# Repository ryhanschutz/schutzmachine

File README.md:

<div align="center">

### Painel Digital de Telemetria Automotiva Stand-Alone — Protocolo CAN / OBD-II
**Hardware aberto embarcado em ESP32-S3 · Display IPS 4.3" (`480 × 272`) · Shift Light físico 10× LEDs 5mm · Carcaça 3D paramétrica em 3 etapas**

<br/>

<table>
  <tr>
    <td align="center" width="52%">
      <br/>
      <sub><b>Simulação em Perspectiva 3/4</b> — Case 3D montado com friso vermelho, tela ativa e 10 LEDs sincronizados</sub>
    </td>
    <td align="center" width="48%">
      <br/>
      <sub><b>Vista Frontal em Operação</b> — Puxada simulada com curva de RPM, peak-hold e flash de shift-light</sub>
    </td>
  </tr>
</table>

*Teste a interface interativa ao vivo no navegador em [`frontend_preview/index.html`](./frontend_preview/index.html)*

</div>

---

## Desenho Técnico Mecânico (ABNT A2 · Escala 1:1 · 1º Diedro)

<div align="center">
  
  <br/>
  <sub>
    <b>Dimensões externas:</b> <code>154.0 × 105.0 × 35.0 mm</code> (+ <code>6.0 mm</code> pés M4) · <b>Autor:</b> Ryhan Schutz ·
    <a href="./docs/desenho_tecnico/case_ft600_polo_desenho_tecnico.dxf"><b>Baixar .DXF (ZWCAD / AutoCAD)</b></a> ·
    <a href="./docs/desenho_tecnico/case_ft600_polo_desenho_tecnico.pdf"><b>Baixar .PDF Vetorial (A2)</b></a>
  </sub>
</div>

---

## Galeria 3D & Engenharia Mecânica

Modelagem paramétrica (`1 unid. = 1 mm`) com **auditoria física interna** para todos os módulos/conectores, **logo gravada em baixo-relevo** (`0.6 mm` frontal / `0.8 mm` traseira) e impressão em **3 peças sem pintura**.

<table>
  <tr>
    <td align="center" width="50%">
      <br/>
      <sub><b>Montagem Final:</b> Contorno ergonômico com aba anti-sol, 10 LEDs 5mm e logo em baixo-relevo</sub>
    </td>
    <td align="center" width="50%">
      <br/>
      <sub><b>Auditoria Interna:</b> PCB 4.3", plugues JST, 10 LEDs 5mm, SN65HVD230, MP1584EN e Buzzer 12mm</sub>
    </td>
  </tr>
  <tr>
    <td align="center" width="50%">
      <br/>
      <sub><b>Vista Explodida:</b> 3 peças da carenagem + subconjunto eletrônico interno</sub>
    </td>
    <td align="center" width="50%">
      <br/>
      <sub><b>Bandeja 3D:</b> 3 arquivos <code>.STL</code> orientados na mesa (<code>Z_min = 0</code>) com malha fechada</sub>
    </td>
  </tr>
  <tr>
    <td align="center" width="50%">
      <br/>
      <sub><b>Etapa 1 (<code>01_tampa_frontal.stl</code>):</b> 10 sedes escalonadas (Ø 6.4 → Ø 5.25 mm) + 8 torres M3</sub>
    </td>
    <td align="center" width="50%">
      <br/>
      <sub><b>Etapa 3 (<code>03_tampa_traseira.stl</code>):</b> Berços snap-fit dedicados + baia rebaixada para GX16-4P (Ø 16.2 mm)</sub>
    </td>
  </tr>
</table>

| Etapa | Arquivo `.STL` | Material / Cor | Prof. | Parâmetros FDM Recomendados |
| :---: | :--- | :---: | :---: | :--- |
| **01** | [`01_tampa_frontal.stl`](./impressao_3d/01_tampa_frontal.stl) | PETG / ABS **Preto** | `12.0 mm` | Bico `0.4` · Camada `0.20` · 4 perímetros · 25% Gyroid |
| **02** | [`02_anel_vermelho.stl`](./impressao_3d/02_anel_vermelho.stl) | PETG / ABS **Vermelho** | `3.0 mm` | Bico `0.4` · Camada `0.16–0.20` · Sem suportes |
| **03** | [`03_tampa_traseira.stl`](./impressao_3d/03_tampa_traseira.stl) | PETG / ABS **Preto** | `20.0 mm` | Bico `0.4` · Camada `0.20` · 4 perímetros · Suporte sob pés M4 |

---

## Arquitetura & Protocolo CAN

Projetado para **qualquer veículo equipado com barramento CAN / OBD-II (ISO 15765-4)**, conectado via **cabo único destacável (`GX16-4P`)** sem corte no chicote original.

```mermaid
flowchart LR
    subgraph CAR["Veículo com Barramento CAN / OBD-II"]
        OBD["Porta OBD-II J1962<br/>Pino 6: CAN-H | Pino 14: CAN-L<br/>Pino 4/5: GND"]
        FUSE["Pós-Chave 12V (Linha 15)<br/>Add-a-Circuit + Fusível 2A"]
    end

    subgraph HARNESS["Cabo Único Destacável"]
        GX16["Conector Traseiro GX16-4P<br/>1: +12V | 2: GND | 3: CAN-H | 4: CAN-L"]
    end

    subgraph CASE["SchutzMachine (154 × 105 × 35 mm)"]
        TVS["TVS (SMBJ18A) +<br/>Step-Down MP1584EN (12V → 5V)"]
        CAN["Transceiver CAN<br/>SN65HVD230 (3.3V)"]
        ESP["Guition JC4827W543C<br/>ESP32-S3 (Core 0: TWAI / Core 1: LVGL)<br/>IPS 4.3&quot; 480×272 + Touch GT911"]
        LEDS["Shift Light Superior<br/>10× LEDs 5mm (4V · 3Vm · 3Az)"]
        BUZ["Buzzer Piezo 12mm"]
    end

    OBD -->|"Par trançado + GND"| GX16
    FUSE -->|"+12V Pós-Chave"| GX16
    GX16 --> TVS -->|"5V Regulado"| ESP
    GX16 --> CAN <-->|"IO17 (TX) / IO18 (RX)"| ESP
    ESP --> LEDS
    ESP --> BUZ
```

### Cálculo de Marcha & Calibração por Veículo

Como cada veículo possui relações de câmbio, diferencial, tamanho de pneu e faixa de giro próprias, a inferência de marcha depende diretamente da calibração do conjunto mecânico:

$$R_n = \frac{\text{RPM}}{\text{Velocidade (km/h)}}$$

- **Calibração Embarcada (NVS):** Gravação das razões $R_n$ por marcha, faixas de *shift-light* (`SPORT` / `ECO`) e limiares de alerta direto na memória não-volátil do ESP32-S3.
- **Software de Calibração (Roadmap):** Desenvolvimento futuro de um aplicativo dedicado (via USB-C / Wi-Fi) para criar perfis por veículo, editar relações de marcha, curvas de LEDs, PIDs customizados e limites térmicos/elétricos.

---

## Hardware, BOM & Pinagem

<table>
  <tr>
    <td align="center" width="50%">
      <br/>
      <sub><b>SN65HVD230 (3.3 V)</b> — <code>16.5 × 14.5 × 6.0 mm</code></sub>
    </td>
    <td align="center" width="50%">
      <br/>
      <sub><b>MP1584EN (12V → 5V)</b> — <code>22.0 × 17.0 × 4.5 mm</code></sub>
    </td>
  </tr>
</table>

| Componente | Especificação | Dimensões (mm) | Função |
| :--- | :--- | :---: | :--- |
| **Display + MCU** | Guition **JC4827W543C** (ESP32-S3 N4R8 · IPS 4.3" · GT911) | `120.0 × 70.2 × 4.7` | Core 0: CAN/TWAI · Core 1: LVGL 9 |
| **Transceiver CAN** | **SN65HVD230** (3,3 V — `IO17` TX / `IO18` RX) | `16.5 × 14.5 × 6.0` | Interface ISO 15765-4 (500 kbps) |
| **Regulador DC-DC** | **D-SUN MP1584EN** + Diodo TVS **SMBJ18A** | `22.0 × 17.0 × 4.5` | Alimentação 12V → 5.00V protegida |
| **Shift Light** | **10× LEDs difusos 5mm** (4 Verde · 3 Vermelho · 3 Azul) | `Ø 5.0 × 8.6` | Barra superior progressiva + flash |
| **Conector / Buzzer** | **GX16-4P** (painel) + Buzzer Piezo `12 mm` | `Ø 16.2` / `Ø 12.0` | Chicote destacável + alerta sonoro |
| **Fixação** | 8× Insertos **M3** (`Ø 4.2`) + 4× Insertos **M4** (`Ø 5.2`) | — | PCB, fechamento e pés traseiros |

<details>
<summary><b>Pinagem Elétrica (GX16-4P & SN65HVD230) e Telemetria OBD-II Mode 0x01</b></summary>
<br/>

| Pino `GX16-4P` | Origem | Destino Interno | Observação |
| :---: | :--- | :--- | :--- |
| **1** | Pós-Chave 12 V (Fusível 2 A) | `MP1584EN IN+` (+ TVS) | Evitar Linha 30 (não drenar bateria) |
| **2** | OBD-II Pino 4/5 (`GND`) | `GND` comum | Referência única |
| **3** | OBD-II Pino 6 (`CAN-H`) | `SN65HVD230 CANH` | Par trançado com Pino 4 |
| **4** | OBD-II Pino 14 (`CAN-L`) | `SN65HVD230 CANL` | Par trançado com Pino 3 |

| Variável | PID OBD-II | Taxa | Variável | PID OBD-II | Taxa |
| :--- | :---: | :---: | :--- | :---: | :---: |
| **RPM** | `0x0C` | 20–40 Hz | **Temp. Água** | `0x05` | 1 Hz |
| **Velocidade** | `0x0D` | 20–40 Hz | **Temp. Ar (IAT)** | `0x0F` | 1 Hz |
| **TPS (Borboleta)** | `0x11` / `0x49` | 10–20 Hz | **Bateria** | `0x42` | 1 Hz |
| **Carga / Avanço IGN** | `0x04` / `0x0E` | 5–10 Hz | **Nível Tanque** | `0x2F` | 0,2 Hz |
| **MAP (Pressão/Vácuo)** | `0x0B` | 5 Hz | **Marcha** | Calculada | Real-time |

> [!WARNING]
> Ative **`PSRAM ECC`** no firmware do ESP32-S3 N4R8 (eleva a operação de `+65 °C` para `+85 °C` no painel ao sol) e **ajuste o MP1584EN para `5.00 V` em bancada** antes de conectar o display.

</details>

---

## Estrutura & Roadmap

```text
schutzmachine/
├── frontend_preview/           # Simulador interativo 480×272 + 10 LEDs 5mm
├── impressao_3d/               # 3 arquivos .STL prontos p/ fatiamento + bandeja Blender
├── docs/
│   ├── desenho_tecnico/        # Prancha ABNT A2 (.DXF p/ ZWCAD, .PDF vetorial e .PNG)
│   └── images/                 # GIFs 3D animados, renders, auditoria interna e fotos HW
├── gerar_case_ft600_polo.py    # Script paramétrico 3D (Blender / bpy)
└── case_ft600_polo.blend       # Montagem 3D completa com eletrônica interna
```

- [x] **Engenharia Mecânica & Case 3D** — Modelagem paramétrica, auditoria interna, gravação da logo e 3 `.STL` fechados
- [x] **Desenho Técnico ABNT A2** — Prancha 1:1 em 1º diedro (`.DXF` nativo para ZWCAD + `.PDF`)
- [x] **Simulador UI & Demos 3D** — Tela `480 × 272` interativa + GIFs da carcaça montada em operação
- [ ] **Firmware ESP32-S3 (LVGL 9 + TWAI CAN)** — Polling OBD-II ativo, renderização 60 FPS e controle dos 10 LEDs
- [ ] **Software de Calibração** — Ferramenta externa para perfis de veículos, relações de marcha, shift-light e alertas
- [ ] **Validação em Bancada & Impressão Final** — Montagem PETG/ABS, insertos M3/M4 e testes em veículo CAN

---

<div align="center">
  <sub>Projeto desenvolvido por <b>Ryhan Schutz</b> · Hardware Aberto & Engenharia Mecânica</sub>
</div>

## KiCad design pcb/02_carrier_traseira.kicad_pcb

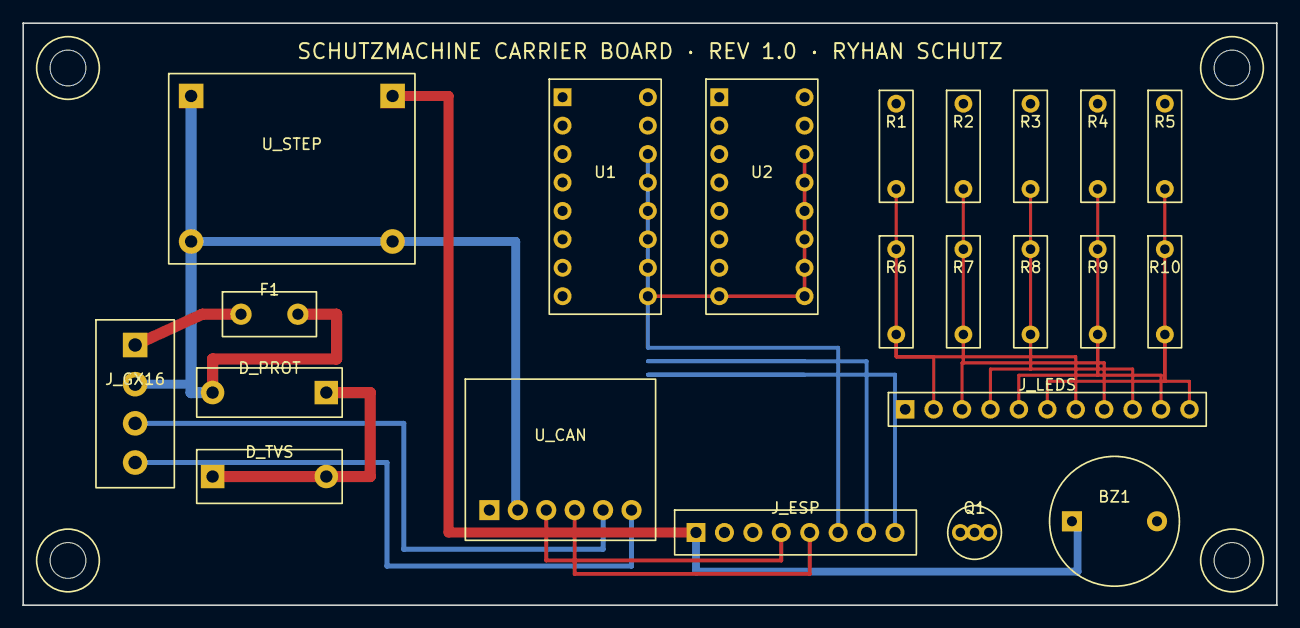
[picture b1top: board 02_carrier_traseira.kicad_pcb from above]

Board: 2 copper layers, 112.0 x 52.0 mm, 22 parts (0 on the bottom side), 36 nets.

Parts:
BZ1: BUZZER_12MM; Buzzer_12mm
D_PROT: 1N5822; Diode_DO201
D_TVS: 1.5KE18A; Diode_TVS_1.5KE18A
F1: PTC_2A; Fuse_PTC_THT
J_ESP: TO_GUITION_ESP32; PinHeader_1x08_2.54mm
J_GX16: GX16-4P_IN; TerminalBlock_4P_3.5mm
J_LEDS: TO_LED_BAR_11P; PinHeader_1x11_2.54mm
Q1: 2N2222; TO-92_2N2222
R1, R2, R3, R4, R5, R6, R7, R8, R9, R10: 220R; R_Axial_220R
U1: 74HC595_1; DIP-16_74HC595
U2: 74HC595_2; DIP-16_74HC595
U_CAN: SN65HVD230; Module_SN65HVD230_Carrier
U_STEP: MP1584EN_5V; Module_MP1584EN_Carrier

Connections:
3V3: J_ESP.2, U1.10, U1.16, U2.10, U2.16, U_CAN.1
+5V: BZ1.1, J_ESP.1, U_STEP.3
+12V_FUSED: D_PROT.1, F1.2
+12V_PROT: D_PROT.2, D_TVS.1, U_STEP.1
+12V_RAW: F1.1, J_GX16.1
BUZ_C: BZ1.2, Q1.3
CAN_H: J_GX16.3, U_CAN.5
CAN_L: J_GX16.4, U_CAN.6
CAN_RX: J_ESP.5, U_CAN.4
CAN_TX: J_ESP.4, U_CAN.3
GND: D_TVS.2, J_ESP.3, J_GX16.2, J_LEDS.1, Q1.1, U1.8, U1.13, U2.8, U2.13, U_CAN.2, U_STEP.2, U_STEP.4
LED1: J_LEDS.2, R1.2
LED2: J_LEDS.3, R2.2
LED3: J_LEDS.4, R3.2
LED4: J_LEDS.5, R4.2
LED5: J_LEDS.6, R5.2
LED6: J_LEDS.7, R6.2
LED7: J_LEDS.8, R7.2
LED8: J_LEDS.9, R8.2
LED9: J_LEDS.10, R9.2
LED10: J_LEDS.11, R10.2
NC: U2.2, U2.3, U2.4, U2.5, U2.6, U2.7, U2.9
SR1_Q0: R1.1, U1.15
SR1_Q1: R2.1, U1.1
SR1_Q2: R3.1, U1.2
SR1_Q3: R4.1, U1.3
SR1_Q4: R5.1, U1.4
SR1_Q5: R6.1, U1.5
SR1_Q6: R7.1, U1.6
SR1_Q7: R8.1, U1.7
SR2_Q0: R9.1, U2.15
SR2_Q1: R10.1, U2.1
SR_CLK: J_ESP.7, U1.11, U2.11
SR_DATA: J_ESP.6, U1.14
SR_LATCH: J_ESP.8, U1.12, U2.12
SR_QH: U1.9, U2.14

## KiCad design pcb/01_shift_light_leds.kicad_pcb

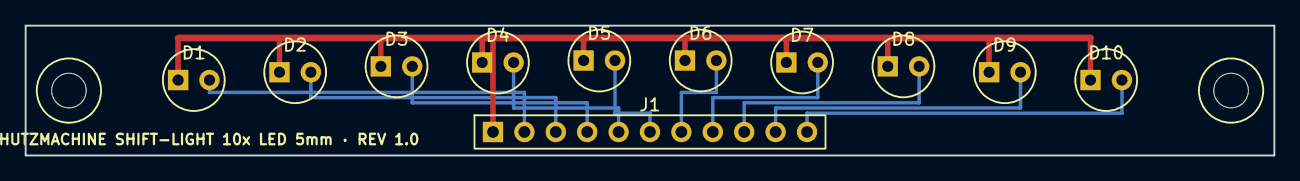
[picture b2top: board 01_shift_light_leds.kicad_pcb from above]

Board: 2 copper layers, 101.0 x 10.5 mm, 11 parts (0 on the bottom side), 11 nets.

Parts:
D1, D2, D3, D4: LED5_V; LED_5mm_V
D5, D6, D7: LED5_Vm; LED_5mm_Vm
D8, D9, D10: LED5_Az; LED_5mm_Az
J1: TO_CARRIER_11P; PinHeader_1x11_2.54mm

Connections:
GND: D1.1, D2.1, D3.1, D4.1, D5.1, D6.1, D7.1, D8.1, D9.1, D10.1, J1.1
LED1: D1.2, J1.2
LED2: D2.2, J1.3
LED3: D3.2, J1.4
LED4: D4.2, J1.5
LED5: D5.2, J1.6
LED6: D6.2, J1.7
LED7: D7.2, J1.8
LED8: D8.2, J1.9
LED9: D9.2, J1.10
LED10: D10.2, J1.11
